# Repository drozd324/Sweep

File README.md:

Below the first two pictures show my modifications to sweep v2.2 .
Below that again is the original readme.

# Sweep
<!--
           ___                        ___
      ___ |   | ___ ___      ___ ___ |   | ___
 ___ |   |`___`|   |   |    |   |   |`___`|   | ___
|   |`___`|   |`___`___`    `___`___`|   |`___`|   |
`___`|   |`___`|   |   |    |   |   |`___`|   |`___`
|   |`___`|   |`___`___`    `___`___`|   |`___`|   |
`___`|   |`___`|   |   |    |   |   |`___`|   |`___`
|   |`___`     `___`___`    `___`___`     `___`|   |
`___`           ___ ___      ___ ___           `___`
               |   |   |    |   |   |
               `___`___`    `___`___`
-->
>    
> <sub>Bluetooth Sweep 2 + MBK Legend Keycaps</sub>

<span>

</span>

## What is sweep?

Sweep is a version of the more fabulous [Ferris](https://github.com/pierrechevalier83/ferris) by [Pierre Chevalier](https://github.com/pierrechevalier83/) that uses a daughter board like a promicro, elite-c, bit-c, nice!nano etc. instead of using onboard components.

## What are the different types?

⭐ Sweep 2 - Recommended Choc v1 board with all the features.  
⭕ Sweep Half Swept - Same as Sweep 2, but with a reversible pro-micro footprint.  
⭕ Sweep Bling MX - An MX only Sweep that features Kailh's hotswap sockets and a stacked case.  
⭕ Sweep Bling LP - A Choc v1 only Sweep that features Kailh's hotswap sockets.  
⭕ Sweep High - Same as the Sweep 2, but trades choc spacing for compatibility with more switches and keycaps.  
⭕ Sweep High M - A soldered MX only Sweep, with a reversible PCB design.  
⭕ Sweep Mini - The only version that supports Choc minis.  

| Device | On/Off Switch<sup>[1]</sup> | Reversible PCB<sup>[2]</sup> | Choc V1 | Choc V2 | Choc Mini | MX & Alps | Choc Spacing<sup>[3]</sup> | Tenting<sup>[4]</sup> | Hot Swap |
| :--- | :---: | :---: | :---: | :---: | :---: | :---: | :---: | :---: | :---: |
| Sweep2.x          | ✔ |   | ✔ |   |   |   | ✔ | ✔ | Mill-Max (optional) |
| Sweep Bling LP    | ✔ |   | ✔ |   |   |   | ✔ | ✔ | Kailh (required) |
| Sweep Bling MX    | ✔ | ✔ |   |   |   | ⚠<br/><sup>[5]</sup> |   | ✔ | Kailh (required) |
| Sweep High        | ✔ |   | ✔ | ✔ |   | ✔ |   | ✔ |
| Sweep High M      | ✔ | ✔ |   |   |   | MX |   | ✔ |   |
| Sweep Half Swept  | ✔ | ✔ | ✔ |   |   |   | ✔ | ✔ | Mill-Max (optional) |
| Sweep Mini        |   | ✔ |   |   | ✔ |   | ✔ |   |

> Note: All versions support bluetooth with Nice!Nano

*<sup>[1]</sup> An on/off switch is recommended for bluetooth builds.*  
*<sup>[2]</sup> With a reversible PCB it's easier to make mistakes during assembly, but it allows you to purchase less boards.*  
*<sup>[3]</sup> Choc spaced boards have the switches in a tighter grid. This provides a better final look but is only compatible with some choc keycaps. (e.g. MBK)*  
*<sup>[4]</sup> Supports splitkb's [tenting puck.](https://splitkb.com/products/tenting-puck?_pos=1&_psq=tenting%20&_ss=e&_v=1.0)*  
*<sup>[5]</sup> MX + kailh hotswap ONLY. Alps are NOT supported.*  

## Components list

To build and use a Sweep you will need:

* 1x PCB Kit
* 2x promicro compatible boards or 2 nice!nanos.
* 34 switches of a compatible type (refer to the compatibility table)
* 34 keycaps
* 2x reset switches (optional; [B3U-1000P(M)](https://github.com/davidphilipbarr/Sweep/issues/20))
* Some little rubber feet/bumpers
* 2x power switches (optional if supported; MSK 12C02)
* 1x TRRS (not TRS!) cable (wired build only)
* 2x TRRS Jack [PJ-320A] (wired build only)
* 1 USB Cable (depends on your micro-controller choice)

## How do I make this thing?

## Firmware

The firmware can be found [with the Ferris  firmware as part of QMK](https://github.com/qmk/qmk_firmware/tree/master/keyboards/ferris/sweep).

Firmware for zmk and bluemicro_ble is called ["Cradio"](https://zmk.dev/docs/hardware/).

## Who made this?

* [Pierre Chevalier](https://github.com/pierrechevalier83)
* [David Barr](https://github.com/davidphilipbarr)
* [Ibnu Daru Aji](https://github.com/ibnuda/)
* [Duccio](https://github.com/duckyb)

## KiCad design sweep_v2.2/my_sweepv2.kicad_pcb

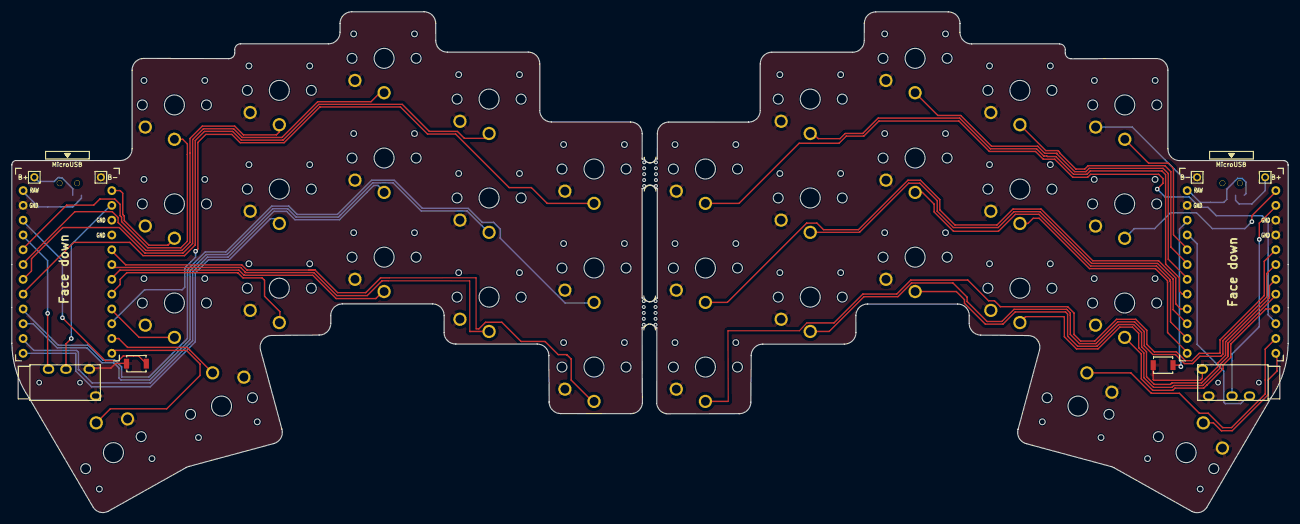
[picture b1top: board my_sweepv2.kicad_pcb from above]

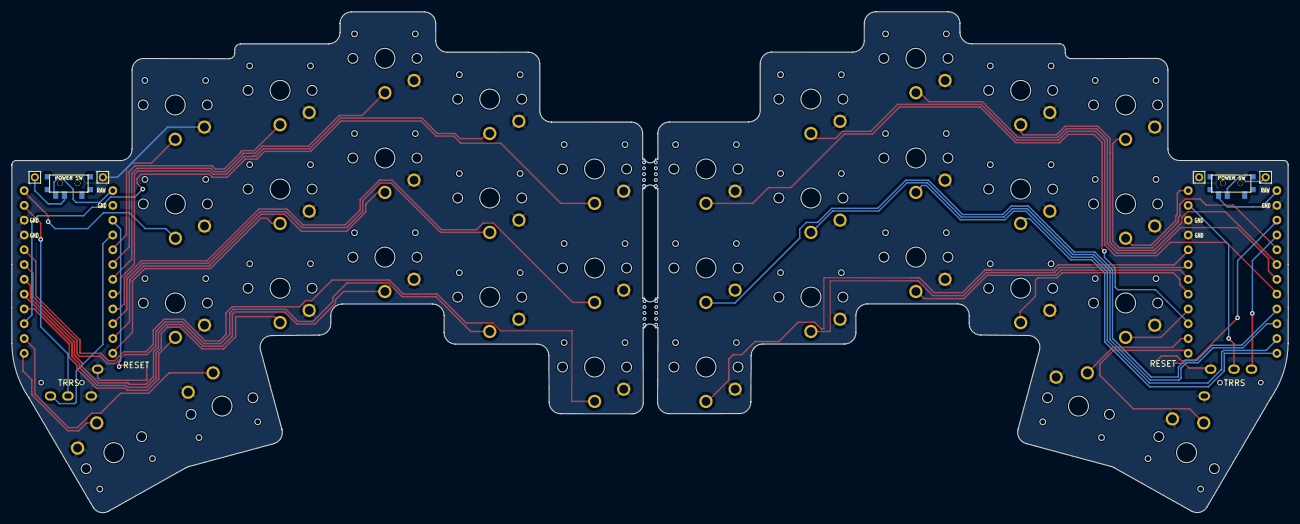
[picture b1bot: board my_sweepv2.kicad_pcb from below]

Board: 2 copper layers, 219.1 x 86.0 mm, 48 parts (2 on the bottom side), 43 nets.

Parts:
B+: MountingHole_Pad; 1pin_conn
B+#2: MountingHole_Pad; 1pin_conn
B-: MountingHole_Pad; 1pin_conn
B-#2: MountingHole_Pad; 1pin_conn
J1, J2: AudioJack4dpb; TRRS-PJ-320A
POWER SW: SW_SPDT; SPDT_C128955
POWER SW#2: SW_SPDT; SPDT_C128955
RSW1, RSW2: SW_Push; SW_SPST_B3U-1000P
SW2, SW2_r1, SW3, SW3_r1, SW4, SW4_r1, SW5, SW5_r1, SW6, SW6_r1, SW7_r1, SW8, SW8_r1, SW9, SW9_r1, SW10, SW11, SW11_r1, SW12, SW12_r1, SW13_r1, SW14, SW15, SW15_r1, SW16, SW16_r1, SW17, SW17_r1, SW18, SW18_r1, SW20, SW20_r1, SW21, SW21_r1: SW_Push; choc-v1-with-millmax
U1, U2: ProMicro-kbd; ProMicro_v3_min
mouse-bite-2mm-slot, mouse-bite-2mm-slot#2: VAL**; mouse-bite-5mm-slot-with-space-for-track

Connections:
BT+: B+#2.1, POWER SW#2.2
BT+_r: B+.1, POWER SW.2
Switch1: SW2.1, U1.10
Switch1_r: SW2_r1.1, U2.10
Switch2: SW3.1, U1.17
Switch2_r: SW3_r1.1, U2.17
Switch3: SW4.1, U1.18
Switch3_r: SW4_r1.1, U2.18
Switch4: SW5.1, U1.19
Switch4_r: SW5_r1.1, U2.19
Switch5: SW6.1, U1.20
Switch5_r: SW6_r1.1, U2.20
Switch6: SW8.1, U1.16
Switch6_r: SW7_r1.1, U2.16
Switch7: SW9.1, U1.15
Switch7_r: SW8_r1.1, U2.15
Switch8: SW10.1, U1.14
Switch8_r: SW9_r1.1, U2.14
Switch9: SW11.1, U1.13
Switch9_r: SW11_r1.1, U2.13
Switch10: SW12.1, U1.1
Switch10_r: SW12_r1.1, U2.1
Switch11: SW14.1, U1.5
Switch11_r: SW13_r1.1, U2.5
Switch12: SW15.1, U1.6
Switch12_r: SW18_r1.1, U2.6
Switch13: SW16.1, U1.7
Switch13_r: SW15_r1.1, U2.7
Switch14: SW17.1, U1.8
Switch14_r: SW16_r1.1, U2.8
Switch15: SW18.1, U1.9
Switch15_r: SW17_r1.1, U2.9
Switch16: SW21.1, U1.11
Switch16_r: SW21_r1.1, U2.11
Switch17: SW20.1, U1.12
Switch17_r: SW20_r1.1, U2.12
Switch18: J2.R1, U1.2
Switch18_r: J1.R1, U2.2
gnd: B-.1, B-#2.1, J1.S, J1.T, J2.S, J2.T, RSW1.1, RSW2.1, SW2.2, SW2_r1.2, SW3.2, SW3_r1.2, SW4.2, SW4_r1.2, SW5.2, SW5_r1.2, SW6.2, SW6_r1.2, SW7_r1.2, SW8.2, SW8_r1.2, SW9.2, SW9_r1.2, SW10.2, SW11.2, SW11_r1.2, SW12.2, SW12_r1.2, SW13_r1.2, SW14.2, SW15.2, SW15_r1.2, SW16.2, SW16_r1.2, SW17.2, SW17_r1.2, SW18.2, SW18_r1.2, SW20.2, SW20_r1.2, SW21.2, SW21_r1.2, U1.3, U1.4, U1.23, U2.3, U2.4, U2.23
raw: POWER SW.3, POWER SW#2.3, U1.24, U2.24
reset: RSW1.2, U1.22
reset_r: RSW2.2, U2.22
vcc: J1.R2, J2.R2, U1.21, U2.21

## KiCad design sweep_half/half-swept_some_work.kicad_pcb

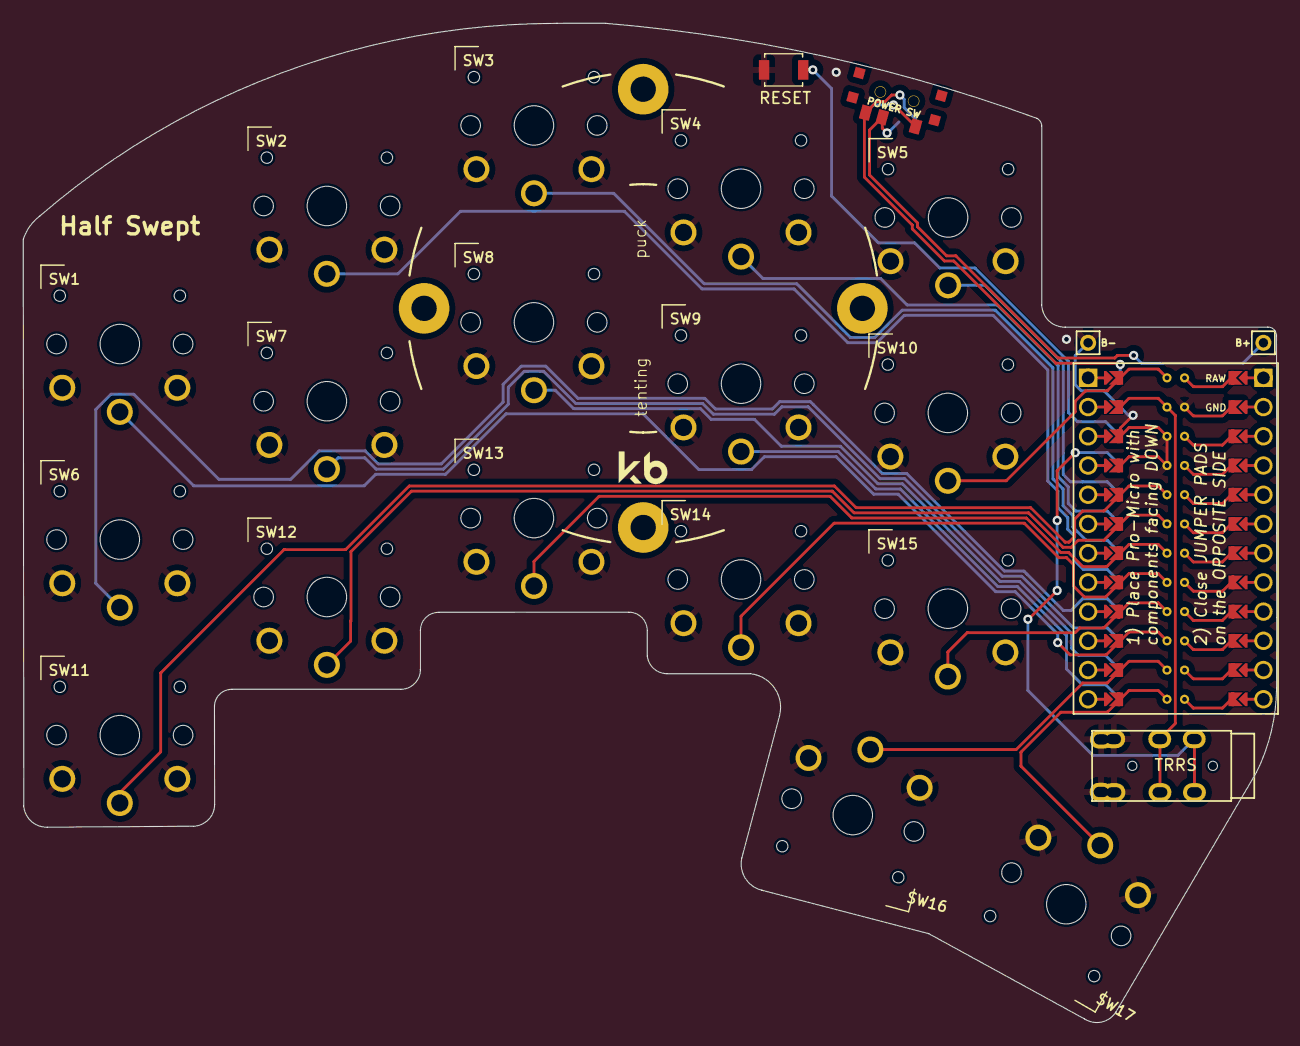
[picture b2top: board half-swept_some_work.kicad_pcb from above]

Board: 2 copper layers, 109.0 x 86.9 mm, 23 parts (0 on the bottom side), 23 nets.

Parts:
B+: MountingHole_Pad; 1pin_conn
B-: MountingHole_Pad; 1pin_conn
J2: AudioJack4dpb; TRRS-PJ-DPB2
POWER SW: SW_SPDT; SPDT_C128955
RSW2: SW_Push; Tactile-Switch_SMT
SW1, SW2, SW3, SW4, SW5, SW6, SW7, SW8, SW9, SW10, SW11, SW12, SW13, SW14, SW15, SW16, SW17: SW_Push; SW_PG1350_rev_DPB
U1: ProMicro-kbd; ProMicro_jumpers_facedown

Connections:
BT+_r: B+.1, POWER SW.2
Switch1: SW1.1, U1.10
Switch2: SW2.1, U1.17
Switch3: SW3.1, U1.18
Switch4: SW4.1, U1.19
Switch5: SW5.1, U1.20
Switch6: SW6.1, U1.16
Switch7: SW7.1, U1.15
Switch8: SW8.1, U1.14
Switch9: SW9.1, U1.13
Switch10: SW10.1, U1.1
Switch11: SW11.1, U1.5
Switch12: SW12.1, U1.6
Switch13: SW13.1, U1.7
Switch14: SW14.1, U1.8
Switch15: SW15.1, U1.9
Switch16: SW16.1, U1.11
Switch17: SW17.1, U1.12
Switch18: J2.R1, U1.2
gnd: B-.1, J2.S, J2.T, RSW2.1, RSW2.2, SW1.2, SW2.2, SW3.2, SW4.2, SW5.2, SW6.2, SW7.2, SW8.2, SW9.2, SW10.2, SW11.2, SW12.2, SW13.2, SW14.2, SW15.2, SW16.2, SW17.2, U1.3, U1.4, U1.23
raw: POWER SW.3, U1.24
reset: RSW2.1, RSW2.2, U1.22
vcc: J2.R2, U1.21

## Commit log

2025-05-16 Removed files I wasnt using and modified the fill of both v2.2 and half
2025-05-16 cleaning and added pictures
2025-05-16 again
2025-05-16 again again
2025-05-16 good now
2025-05-29 fixed trace outside of pcb, started making case
